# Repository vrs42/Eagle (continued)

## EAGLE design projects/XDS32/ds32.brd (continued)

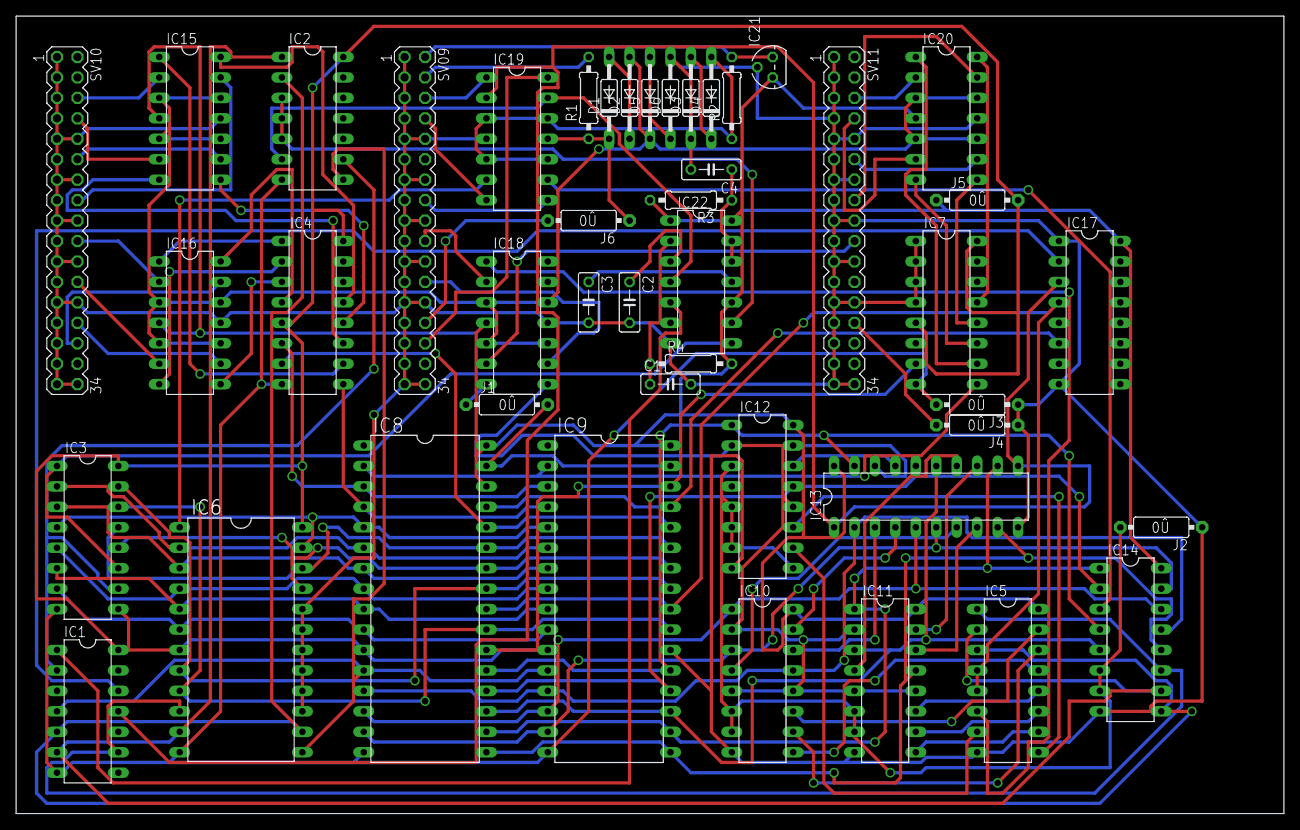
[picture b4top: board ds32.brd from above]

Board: 2 copper layers, 157.5 x 99.1 mm, 45 parts (0 on the bottom side), 109 nets.

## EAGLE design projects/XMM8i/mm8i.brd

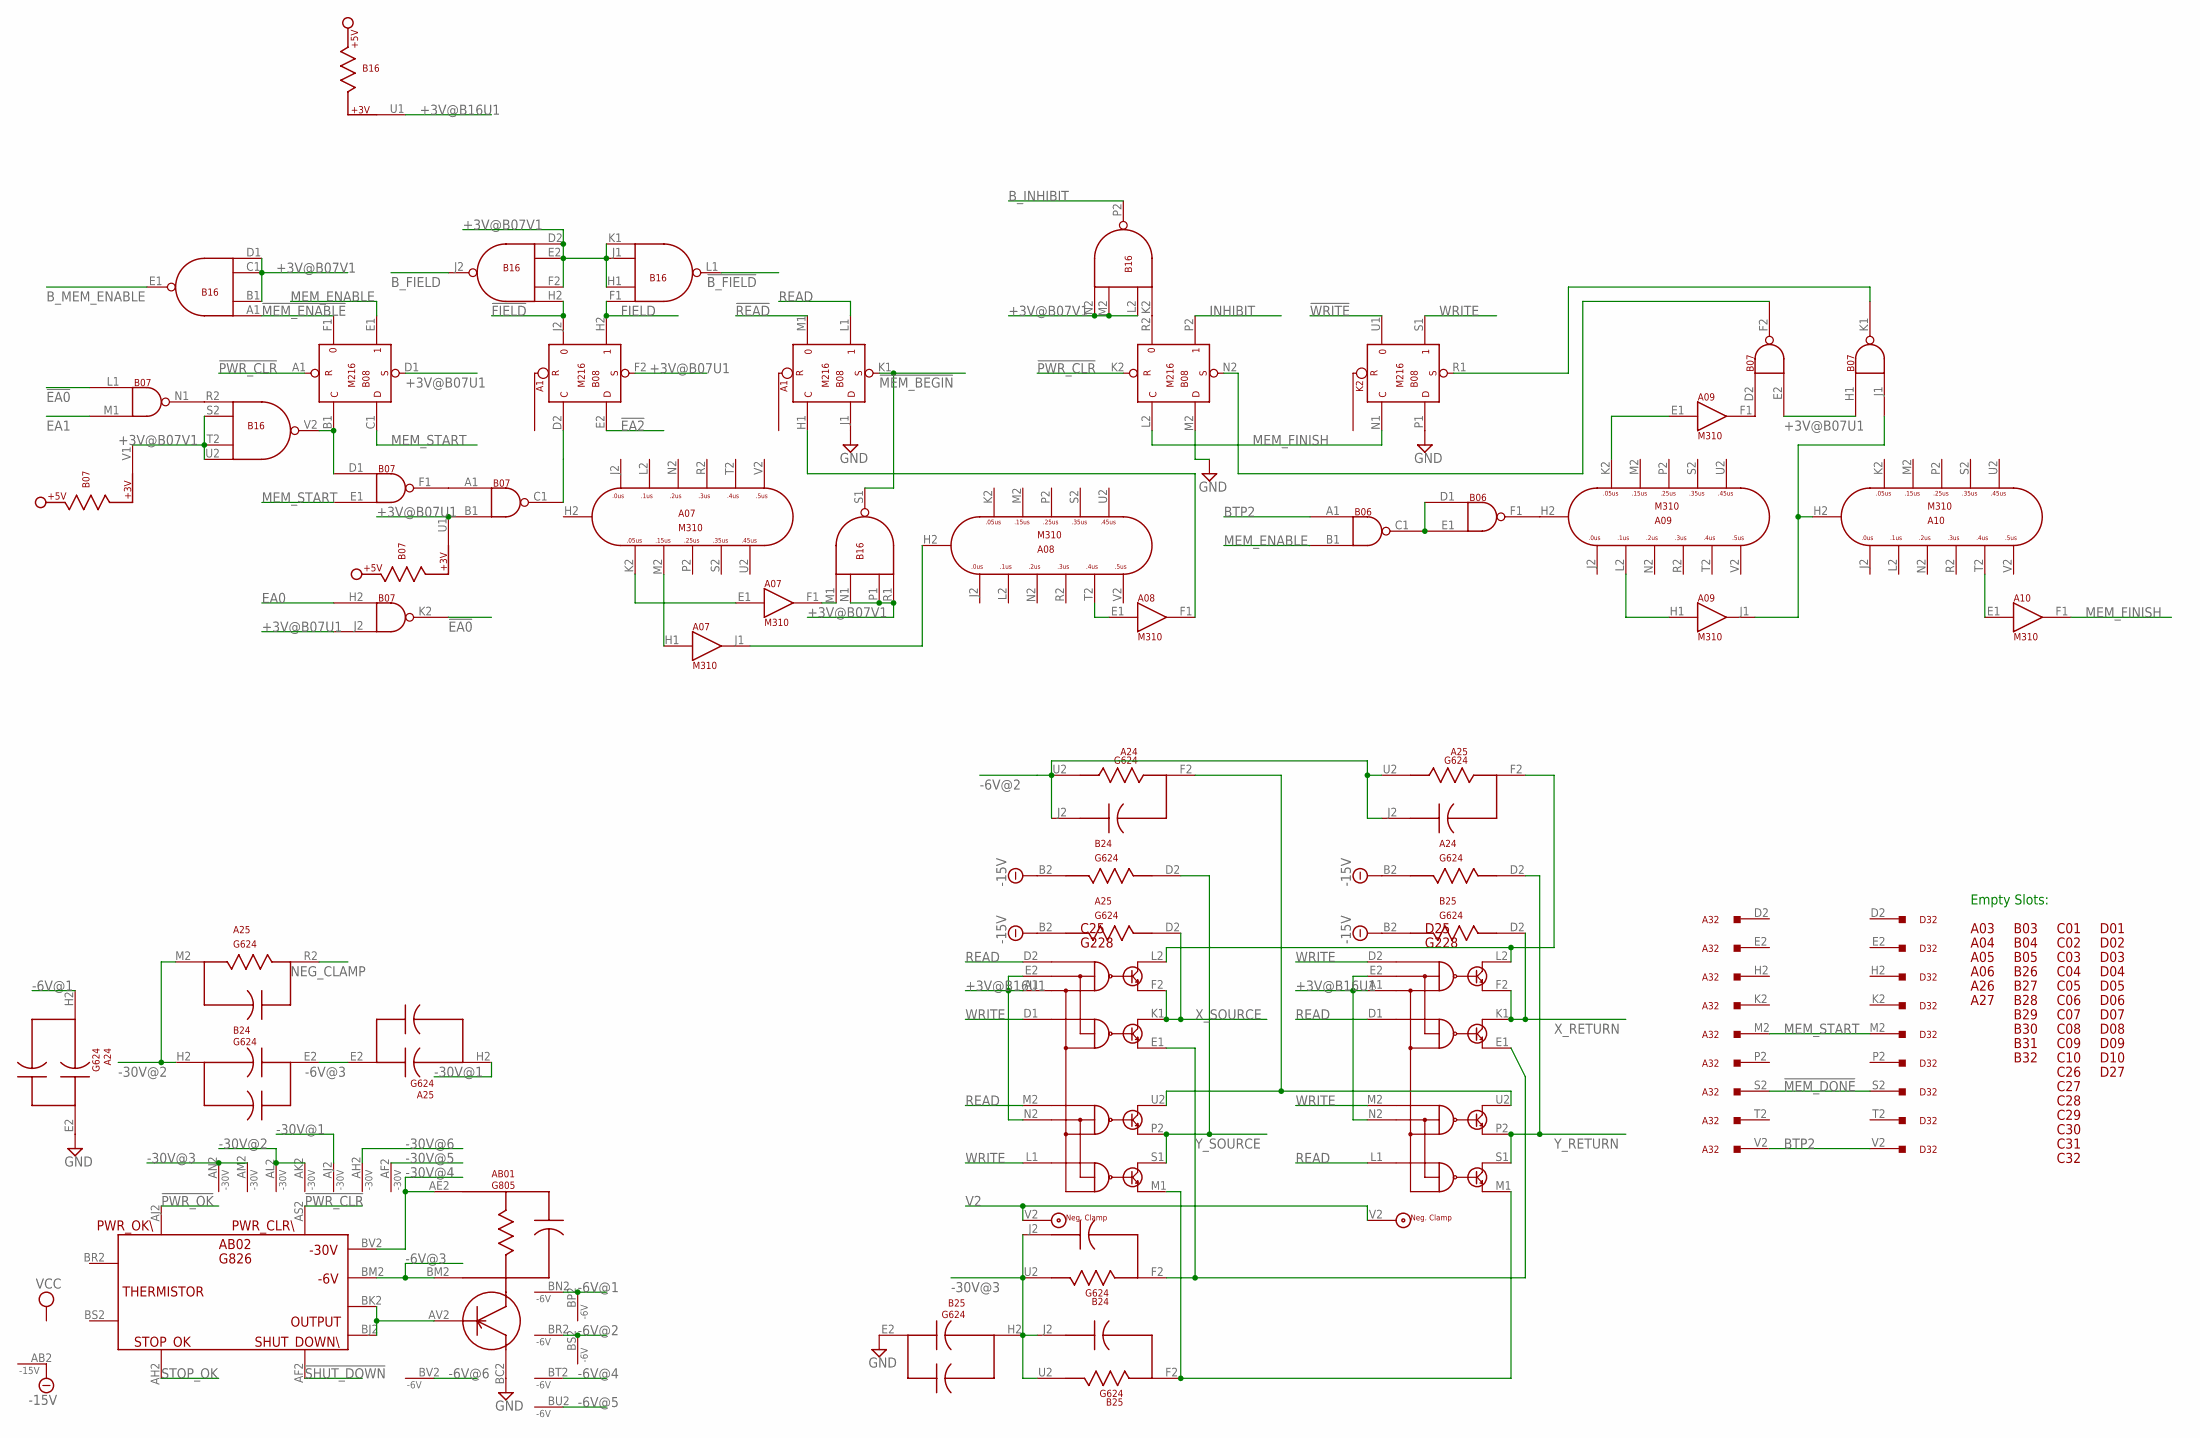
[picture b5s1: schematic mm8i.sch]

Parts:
A03, A04, A05, A06, A26, A27: H807
A07, A08, A09, A10: M310; H807
A24, A25: G624; H807
A32: W033; H807
AB01: G805; H807-2
AB02: G826; H807-2
B03, B04, B05, B26, B27, B28, B29, B30, B31, B32: H807
B06, B07: M113; H807
B08: M216; H807
B16: M617; H807
B24, B25: G624; H807
C01, C02, C03, C04, C05, C06, C07, C08, C09, C10, C26, C27, C28, C29, C30, C31, C32: H807
C25: G228; H807
D01, D02, D03, D04, D05, D06, D07, D08, D09, D10, D27: H807
D25: G228; H807
D32: W033; H807

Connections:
!B_FIELD: B16.L1 (OUT)
!EA0: B07.K2 (OUT), B07.L1 (IN1)
!EA2: B08.E2 (D)
!FIELD: B08.J2 (0), B16.H2 (IN4)
!MEM_BEGIN: B08.K1 (S), B16.S1 (OUT)
!MEM_DONE: A32.S2, D32.S2
!MEM_ENABLE: B08.F1 (0), B16.A1 (IN1)
!PWR_CLR: AB02.AS2, B08.A1 (R), B08.K2 (R)
!PWR_OK: AB02.AJ2
!READ: B08.M1 (0)
!SHUT_DOWN: AB02.AF2
!WRITE: B08.U1 (0)
+3V@B07U1: B07.B1 (IN2), B07.E2 (IN2), B07.H1 (IN1), B07.J2 (IN2), B07.U1, B08.D1 (S), B08.F2 (S)
+3V@B07V1: B07.V1, B16.B1 (IN2), B16.C1 (IN3), B16.D1 (IN4), B16.D2 (IN1), B16.E2 (IN2), B16.F2 (IN3), B16.H1 (IN2), B16.J1 (IN3), B16.K1 (IN4), B16.L2 (IN2), B16.M2 (IN3), B16.N1 (IN2), B16.N2 (IN4), B16.P1 (IN3), B16.R1 (IN4), B16.S2 (IN2), B16.T2 (IN3), B16.U2 (IN4)
+3V@B16U1: B16.U1, C25.A1, C25.E2, C25.N2, D25.A1, D25.E2, D25.N2
-6V@1: A24.H2, AB01.BN2 (-6V), AB01.BP2 (-6V)
-6V@2: A24.J2, A24.U2, A25.J2, A25.U2, AB01.BR2 (-6V), AB01.BS2 (-6V)
-6V@3: A25.E2, AB01.BM2 (-6V), AB02.BM2 (-6V), B24.E2
-6V@4: AB01.BT2 (-6V)
-6V@5: AB01.BU2 (-6V)
-6V@6: AB01.BV2 (-6V)
-15V: A24.B2, A25.B2, AB02.AB2 (-15V), B24.B2, B25.B2
-30V@1: A25.H2, AB01.AJ2 (-30V)
-30V@2: A25.M2, AB01.AK2 (-30V), AB01.AL2 (-30V), B24.H2
-30V@3: AB01.AM2 (-30V), AB01.AN2 (-30V), B24.J2, B24.U2, B25.H2, B25.J2, B25.U2
-30V@4: AB01.AE2 (-30V), AB02.BV2 (-30V)
-30V@5: AB01.AF2 (-30V)
-30V@6: AB01.AH2 (-30V)
BTP2: A32.V2, B06.A1 (IN1), D32.V2
B_FIELD: B16.J2 (OUT)
B_INHIBIT: B16.P2 (OUT)
B_MEM_ENABLE: B16.E1 (OUT)
EA0: B07.H2 (IN1)
EA1: B07.M1 (IN2)
FIELD: B08.H2 (1), B16.F1 (IN1)
GND: A07.C2 (GND), A07.T1 (GND), A08.C2 (GND), A08.T1 (GND), A09.C2 (GND), A09.T1 (GND), A10.C2 (GND), A10.T1 (GND), A24.E2, A32.C2 (GND), A32.F2 (GND), A32.J2 (GND), A32.L2 (GND), A32.N2 (GND), A32.R2 (GND), A32.U2 (GND), AB01.AP2 (GND), AB01.AR2 (GND), AB01.AS2 (GND), AB01.AT2 (GND), AB01.AU2 (GND), AB01.BC2 (GND), AB01.BD2 (GND), AB01.BE2 (GND), AB01.BF2 (GND), AB01.BH2 (GND), AB01.BJ2 (GND), AB01.BK2 (GND), AB01.BL2 (GND), AB02.AC2 (GND), AB02.BC2 (GND), B06.C2 (GND), B06.T1 (GND), B07.C2 (GND), B07.T1 (GND), B08.C2 (GND), B08.J1 (D), B08.M2 (D), B08.P1 (D), B08.T1 (GND), B16.C2 (GND), B16.T1 (GND), B25.E2, C25.C2 (GND), C25.T1 (GND), D25.C2 (GND), D25.T1 (GND), D32.C2 (GND), D32.F2 (GND), D32.J2 (GND), D32.L2 (GND), D32.N2 (GND), D32.R2 (GND), D32.U2 (GND)
INHIBIT: B08.P2 (1)
MEM_ENABLE: B06.B1 (IN2), B08.E1 (1)
MEM_FINISH: A10.F1 (OUT), B08.L2 (C), B08.N1 (C)
MEM_START: A32.M2, B07.E1 (IN2), B08.C1 (D), D32.M2
unnamed: AB01.AV2, AB02.BJ2, AB02.BK2
unnamed: B06.C1 (OUT), B06.D1 (IN1), B06.E1 (IN2)
unnamed: A25.F2, C25.L2, D25.L2
unnamed: A24.F2, C25.U2, D25.U2
unnamed: B07.N1 (OUT), B16.R2 (IN1)
unnamed: B07.D1 (IN1), B08.B1 (C), B16.V2 (OUT)
unnamed: B07.A1 (IN1), B07.F1 (OUT)
unnamed: B07.C1 (OUT), B08.D2 (C)
unnamed: A07.H1 (IN), A07.M2
unnamed: A07.E1 (IN), A07.K2
unnamed: A07.F1 (OUT), B16.M1 (IN1)
unnamed: A07.J1 (OUT), A08.H2
unnamed: A08.E1 (IN), A08.T2
unnamed: A08.F1 (OUT), B08.H1 (C)
unnamed: A09.H2, B06.F1 (OUT)
unnamed: A09.E1 (IN), A09.K2
unnamed: A09.H1 (IN), A09.L2
unnamed: A09.F1 (OUT), B07.D2 (IN1)
unnamed: B25.F2, C25.M1, D25.M1
unnamed: B24.F2, C25.E1, D25.E1
unnamed: B07.F2 (OUT), B08.N2 (S)
unnamed: B08.R2 (0), B16.K2 (IN1)
unnamed: A09.J1 (OUT), A10.H2, B07.J1 (IN2)
unnamed: A10.E1 (IN), A10.T2
unnamed: B07.K1 (OUT), B08.R1 (S)
NEG_CLAMP: A25.R2
READ: B08.L1 (1), C25.D2, C25.M2, D25.D1, D25.L1
STOP_OK: AB02.AH2
V2: C25.V2, D25.V2
VCC: A07.A2 (VCC), A08.A2 (VCC), A09.A2 (VCC), A10.A2 (VCC), AB02.AA2 (VCC), AB02.BA2 (VCC), B06.A2 (VCC), B07.A2 (VCC), B08.A2 (VCC), B16.A2 (VCC), C25.A2 (VCC), D25.A2 (VCC)
WRITE: B08.S1 (1), C25.D1, C25.L1, D25.D2, D25.M2
X_RETURN: B25.D2, D25.F2, D25.K1
X_SOURCE: A25.D2, C25.F2, C25.K1
Y_RETURN: A24.D2, D25.P2, D25.S1
Y_SOURCE: B24.D2, C25.P2, C25.S1

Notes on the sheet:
Empty Slots:

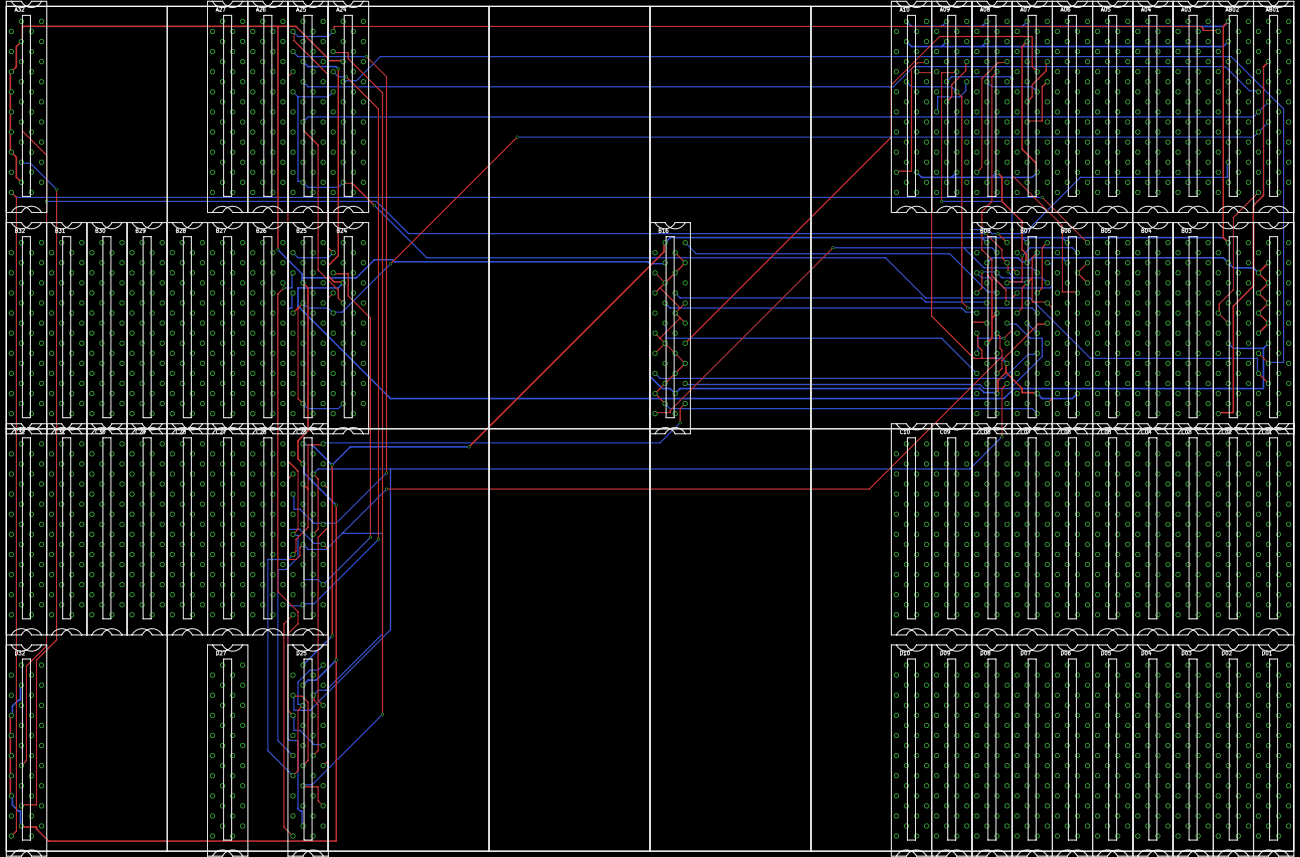
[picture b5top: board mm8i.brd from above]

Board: 2 copper layers, 406.4 x 266.7 mm, 78 parts (0 on the bottom side), 56 nets.

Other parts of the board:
U$1, U$2, U$3, U$4, U$5, U$6, U$7, U$8, U$9, U$10, U$11, U$12, U$13, U$14, U$15, U$16: CBLOCK
